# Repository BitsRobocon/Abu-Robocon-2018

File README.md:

# Abu-Robocon-2018

This Repository contains all the code and CAD models prepared for the Abu-Robocon competition of 2018

## Official Problem Statement

https://aws.robu.in/wp-content/uploads/2017/07/aburobocon2018-rule-book-1.pdf

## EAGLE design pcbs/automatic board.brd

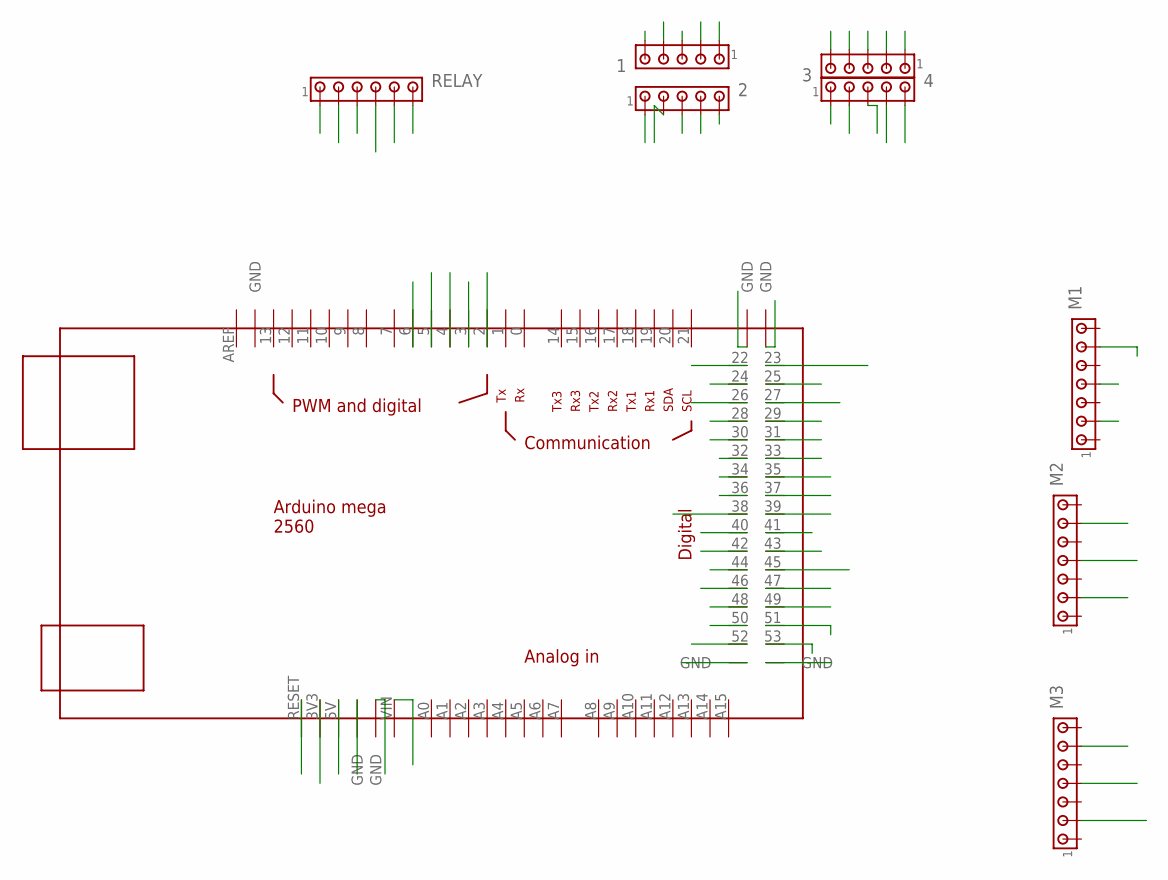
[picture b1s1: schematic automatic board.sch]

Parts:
1, 2, 3, 4: MTA05-100; 10X05MTA
M1, M2, M3: MTA07-100; 10X07MTA
RELAY: MTA06-100; 10X06MTA
U$1: MEGA_DEVICE; MEGAOUTLINE

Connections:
2: M3.4, U$1.2
3: M2.4, U$1.3
3.3: U$1.3V3
4: M1.4, U$1.4
5: U$1.5
6: U$1.6
22: M1.2, U$1.22
23: 1.5, U$1.23
24: M1.6, U$1.24
25: 1.4, U$1.25
26: M2.2, U$1.26
27: 1.3, U$1.27
28: M2.6, U$1.28
29: 1.2, U$1.29
30: M3.2, U$1.30
31: 2.4, U$1.31
32: M3.6, U$1.32
33: 2.3, U$1.33
34: RELAY.2, U$1.34
35: 2.2, U$1.35
36: RELAY.3, U$1.36
37: 2.1, U$1.37
38: RELAY.4, U$1.38
39: 3.5, U$1.39
40: RELAY.5, U$1.40
41: 3.4, U$1.41
42: U$1.42
43: 3.3, U$1.43
44: U$1.44
45: 3.2, U$1.45
46: U$1.46
47: 4.4, U$1.47
48: U$1.48
49: 4.3, U$1.49
50: U$1.50
51: 4.2, U$1.51
52: 4.1, U$1.52
53: U$1.53
GND: 1.1, 3.1, RELAY.6, U$1.GND@2 (GND), U$1.GND@3 (GND), U$1.GND@6 (GND), U$1.GND@7 (GND)
RESET: U$1.RESET
VCC1: RELAY.1, U$1.5V
VCC2: U$1.GND@4 (GND)
VCC3: 2.5, 4.5, U$1.GND@5 (GND)
VIN: U$1.VIN

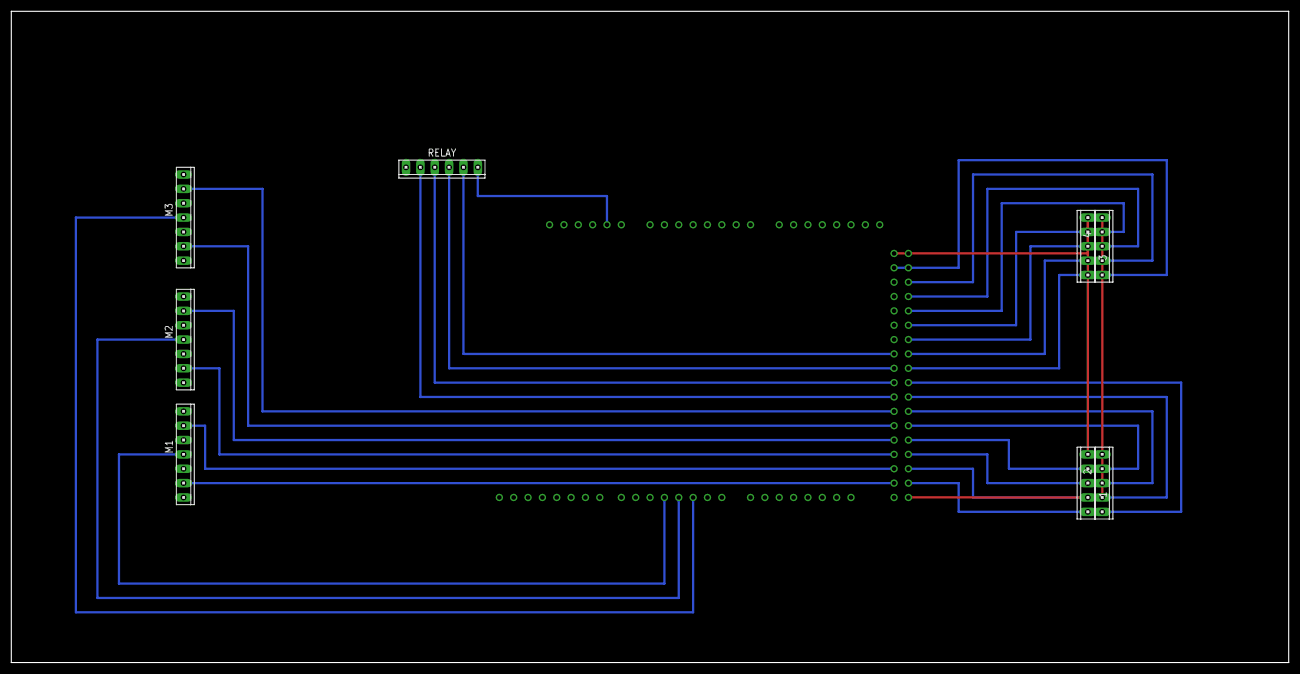
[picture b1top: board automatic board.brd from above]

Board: 2 copper layers, 226.0 x 115.2 mm, 9 parts (1 on the bottom side), 32 nets.

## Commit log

2018-12-14 Adding completed files
2022-11-06 Add files via upload
    Added additional Robocon 2018 codes
